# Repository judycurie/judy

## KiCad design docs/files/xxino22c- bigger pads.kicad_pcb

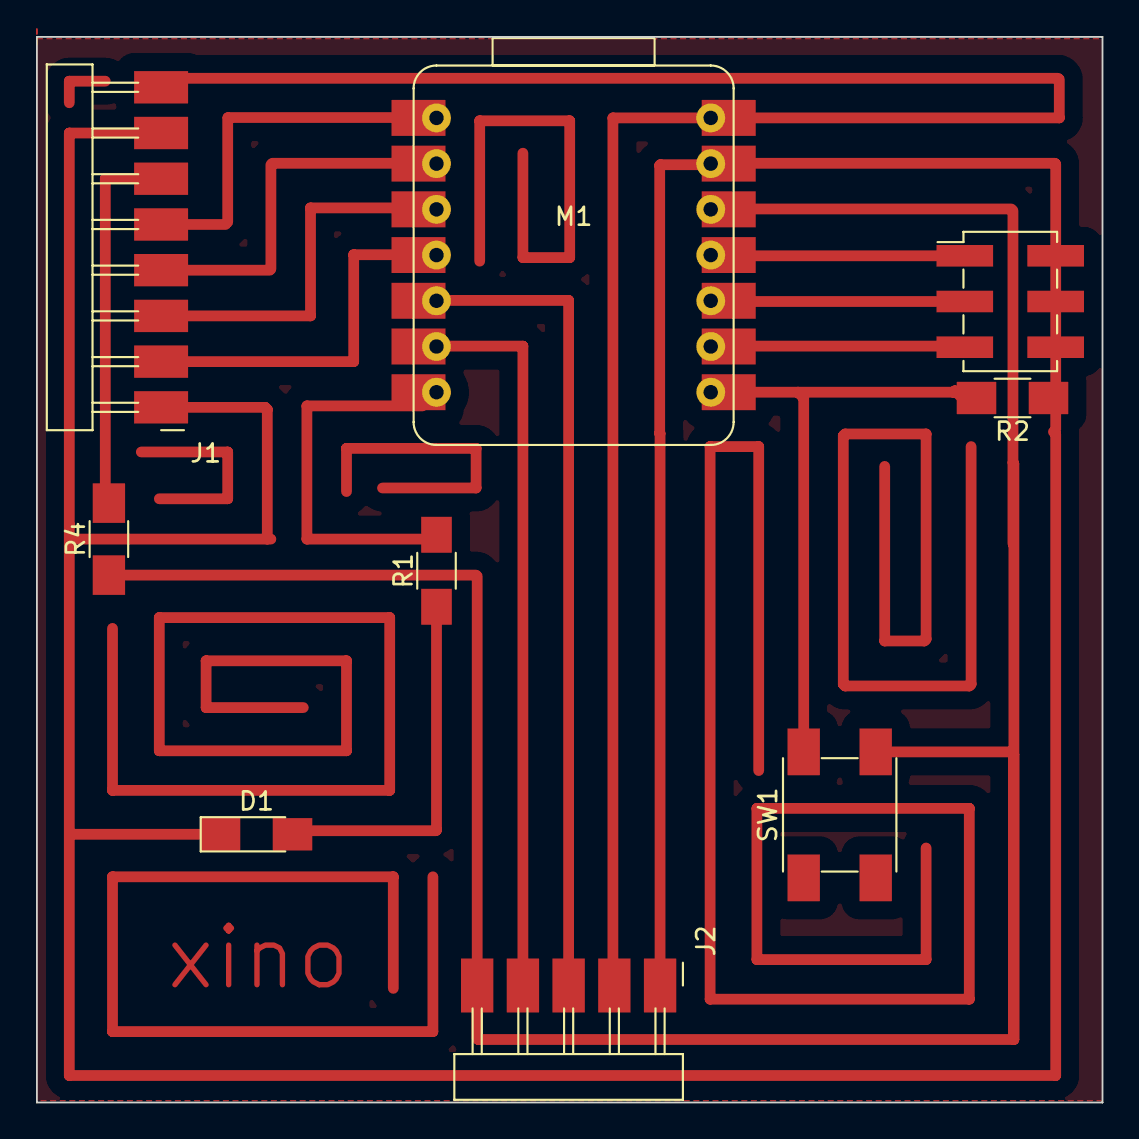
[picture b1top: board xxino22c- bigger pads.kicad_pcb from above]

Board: 2 copper layers, 59.2 x 59.2 mm, 9 parts (0 on the bottom side), 15 nets.

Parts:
D1: LED_1206
J1: Conn_PinHeader_1x08_P2.54mm_Horizontal_SMD; PinHeader_1x08_P2.54mm_Horizontal_SMD
J2: Conn_PinHeader_1x05_P2.54mm_Horizontal_SMD; PinHeader_1x05_P2.54mm_Horizontal_SMD
J3: Conn_PinHeader_2x03_P2.54mm_Vertical_SMD; PinHeader_2x03_P2.54mm_Vertical_SMD
M1: Module_XIAO-RP2040; SeedStudio_XIAO
R1: R_1000; R_1206
R2: R_500; R_1206
R4: R_0; R_1206
SW1: Button_Omron_B3SN_6.0x6.0mm

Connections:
AD0: J1.5, M1.1 (D0)
AD1: J1.4, M1.2 (D1)
AD2: J1.3, M1.3 (D2)
AD3: J1.2, M1.4 (D3)
D4/SDL: J2.3, M1.5 (D4)
D5/SCL: J2.4, M1.6 (D5)
D6/TX: M1.7 (D6), R1.2
D7: M1.8 (D7), R2.2, SW1.1
D8: J3.5, M1.9 (D8)
D9: J3.3, M1.10 (D9)
D10: J3.1, M1.11 (D10)
unnamed: D1.2 (A), R1.1
PWR_3V3: J1.6, J2.5, M1.12 (3V3), R4.1, R4.2, SW1.2
PWR_5V: J1.8, J2.2, M1.14 (5V)
PWR_GND: D1.1 (K), J1.1, J1.7, J2.1, J3.2, J3.4, J3.6, M1.13 (GND), R2.1

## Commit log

2023-01-24 Initial commit from student template
2023-01-25 adding random file
2023-01-26 changing the public folder
2023-01-26 Replace .gitlab-ci.yml
2023-01-26 Adding mkdocs file for integration
2023-01-26 Adding txt file for mkdoc integration
2023-01-26 Add new directory
2023-01-27 adding mkdocs template & student agreement
2023-01-27 new personal website
2023-01-31 Replace mkdocs.yml
2023-01-31 change you did
2023-02-06 week2
2023-02-07 week02
2023-02-07 video
2023-02-07 FFP-logo
2023-02-12 week03
2023-02-16 adding week4
2023-02-22 adding week 4 - final project
2023-02-27 week5-part1
2023-02-28 week5-update
2023-03-08 week06
2023-03-15 week7
2023-03-22 week08
2023-03-27 week09
2023-03-31 week10
2023-04-12 week10-2
2023-04-19 week11
2023-04-26 week12
2023-05-03 week13
2023-05-10 week14
2023-05-17 week15
2023-05-17 week1*
2023-05-17 links*
2023-05-19 week02*
2023-05-19 week03*
2023-05-19 week04*
2023-05-19 week06*
2023-05-19 week08*
2023-05-19 week14*
2023-06-04 final
2023-06-14 presentation
2023-09-12 videos?
2024-02-16 Create CNAME
2024-02-16 Update CNAME
2024-02-16 Deployed be94c28 with MkDocs version: 1.4.3
